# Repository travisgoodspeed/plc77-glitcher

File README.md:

Howdy y'all,

As I write this in 2021, glitching is all the rage in hardware
security again, but twenty years ago in the satellite TV cracking
community it was just as popular, with hand-etched PCBs of
through-hole components being used to glitch smart cards and freely
watch TV.

As Tripod begins to bitrot and this history slowly becomes lost to us,
I thought I'd grab an old glitcher from a [Tripod
website](http://dark-agent_drdss.tripod.com/drdss/id7.html), convert
it to Kicad, and maybe assemble a few glitchers from that age.  This
one is by LPC77, dating from April of 2001.

--Travis

## Organization

The root directory is a [Kicad](https://www.kicad.org/) project,
restored from the original design but without modernizations such as
surface-mount componenets that would alter its asthetics.

The `past` directory contains the published source files, originally
in Eagle's old binary format.  I used Eagle 6.6.0 under Wine to
convert the files into the modern XML format, which Kicad can freely
import.

## Original README Follows

Revisons:
I have increased the length of the circuit board by 1/2 inch 
to allow for a less cluttered layout.

I moved the surface mount resistors nearer to the thru hole types.

I also (the Most Significant change) modified the oscilator circuit
to add a resistor(R6) and change the value of R1, making the output
wave form much better.

Parts list and Notes

```
1 ISO card socket of your choosing
1 9 pin female D sum min connector (X2)
2 1n4004 diodes (D2, D3)
2 1n914 or 1n4148 diodes (D4, D5)
1 red/dreen led (two lead type) (D1)
1 90S2313p-10 atmel processor (IC1)programmed with bl.hex
1 MAX232 (IC3)
1 74HC00 (IC4) 
1 7405 (IC2)
1 7805T (U1)
1 bridge rectifyer (B1)
2 .1uf cap (C1, C3)
2 27pf cap (C4, C5)
1 35uf to 100 uf Cap 16v min (C2)
4 10 uf 16v cap (C6, C8, C9, C10)
2 430 to 475 ohm resister(R3 or R3a,R4 or R4a)
1 1 Meg ohm resister (R1 or R1a)
1 33ohm 1/2 watt resister (R2)
1 1K to 2.2K resister (R5 or R5a)
1 2.2K resister (R6 or R6a)
1 3.57595 mhz Crystal (Q1)
```

This programmer is intended to be used as a standalone Phoenix type
ISO programmer with the ability to use the Atmel Chip from the
Simpleboot product to allow operation with H cards that have suffered
the Black Sunday ECM.

If non Glitching operation is desired, simply do not install the Atmel
IC and put a jumper wire from pin 12 to 13 of that atmels socket.

It is designed to be built on a single sided pcb but there are a few
jumpers that must be installed.

The original one used surface mounted resister and i have added
provisions for thru hole parts, use one or the other not both!

I recommend that all the ICs be socketed.

If you wish to power the programmer from the PC, use a pc power
extension from Radio Shack and cut off one of the male plugs and
attach the red wire to the pad which goes to the diode and the black
wires to the two center pads, the yellow wire it not used but may be
soldered to the pad provided.

If powered from PC, the bridge, regulator and associated parts may be
removed.

I designed the layout to fit the four inch wide opening typical of the
diskette drive in a PC.  I mounted a programer on the plastic type
adapter used to mount a diskette drive in a 5 1/4 inch bay of a PC
with great success.

In an AT type PC it is possible to attach the comm port from the
motherboard to the internally mounted by moving the connector from the
pc's back panel or slot cover. This make for a very neat Emulation
setup.

I have added a slightly modified layout to the package that may be a
little easier to build as it is a little larger and not so
crowded. Take a look at Glitchprog1LedB.brd, the schematic is
identical so i did not duplicate it.

This is my first attempt at releasing a design so pardon my
errors. Your comments are appreiciated, I will learn from them.

 PLC77

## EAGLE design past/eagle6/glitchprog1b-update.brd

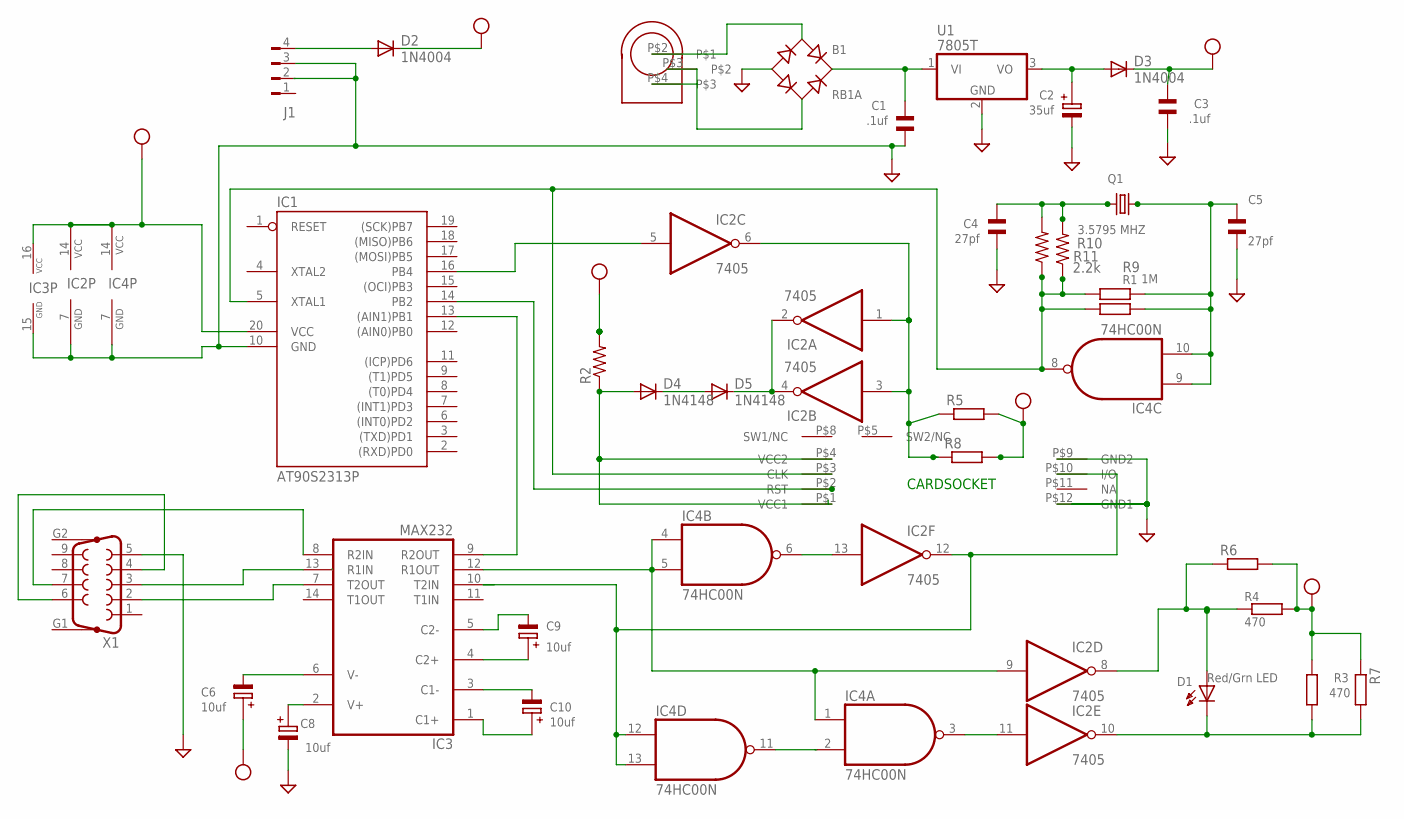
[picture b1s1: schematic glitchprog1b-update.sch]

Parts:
B1: RB1A
C1, C3: .1uf; C5B3
C2: 35uf; E2,0-5
C4, C5: 27pf; C5B3
C6, C8, C9, C10: 10uf; E2,0-5
CDR1: CHEAPREADR; CHEAPREA
D1: Red/Grn LED; LED2
D2, D3: 1N4004; DO41-10
D4, D5: 1N4148; DO35-10
IC1: AT90S2313P; DIL20
IC2: 7405; DIL14
IC3: MAX232; DIL16
IC4: 74HC00N; DIL14
J1: FLOPPY-4
Q1: 3.5795 MHZ; HC49U-V
R1: 1M; 1210
R2: R-US_0207/10; 0207/10
R3: 470; 1210
R4: 470; 1210@2
R5: R-EU_R2010; R2010
R6, R7, R8, R9: R-EU_0204/7; 0204/7
R10: R-US_0204/7; 0204/7
R11: 2.2k; M1206
U1: 7805T; TO220H
U$7: POWER1
X1: F09HP

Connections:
GND: B1.-, C1.1, C2.-, C3.1, C4.1, C5.1, C8.-, CDR1.P$9 (GND2), CDR1.P$12 (GND1), IC1.10 (GND), IC2.7 (GND), IC3.15 (GND), IC4.7 (GND), J1.3, U1.2 (GND), X1.5
unnamed: C9.-, IC3.5 (C2-)
unnamed: IC2.1 (I), IC2.3 (I), IC2.6 (O), R5.1, R8.1
unnamed: C10.-, IC3.3 (C1-)
unnamed: C10.+, IC3.1 (C1+)
unnamed: C9.+, IC3.4 (C2+)
unnamed: C6.-, IC3.6 (V-)
unnamed: C8.+, IC3.2 (V+)
unnamed: C4.2, Q1.1, R10.2, R11.2
unnamed: IC1.13 ((AIN1)PB1), IC3.9 (R2OUT)
unnamed: CDR1.P$3 (CLK), IC1.5 (XTAL1), IC4.8 (O), R1.1, R9.1, R10.1, R11.1
unnamed: D4.K (C), D5.A
unnamed: CDR1.P$2 (RST), IC1.14 (PB2)
unnamed: IC3.8 (R2IN), X1.7
unnamed: B1.+, C1.2, U1.1 (VI)
unnamed: X1.4, X1.6
unnamed: D1.A, IC2.8 (O), R4.1, R6.1
unnamed: CDR1.P$10 (I/O), IC2.12 (O), IC3.10 (T2IN), IC4.12 (I0), IC4.13 (I1)
unnamed: CDR1.P$1 (VCC1), CDR1.P$4 (VCC2), D4.A, R2.1
unnamed: IC3.7 (T2OUT), X1.2
unnamed: D5.K (C), IC2.2 (O), IC2.4 (O)
unnamed: IC2.9 (I), IC3.12 (R1OUT), IC4.1 (I0), IC4.4 (I0), IC4.5 (I1)
unnamed: D1.K, IC2.10 (O), R3.1, R7.2
unnamed: B1.AC1, U$7.P$2
unnamed: B1.AC2, U$7.P$3, U$7.P$4
unnamed: IC2.13 (I), IC4.6 (O)
unnamed: C5.2, IC4.9 (I0), IC4.10 (I1), Q1.2, R1.2, R9.2
unnamed: IC4.2 (I1), IC4.11 (O)
unnamed: IC3.13 (R1IN), X1.3
unnamed: IC1.16 (PB4), IC2.5 (I)
unnamed: IC2.11 (I), IC4.3 (O)
unnamed: C2.+, D3.A, U1.3 (VO)
unnamed: D2.A, J1.4
VCC: C3.2, C6.+, D2.K (C), D3.K (C), IC1.20 (VCC), IC2.14 (VCC), IC3.16 (VCC), IC4.14 (VCC), R2.2, R3.2, R4.2, R5.2, R6.2, R7.1, R8.2

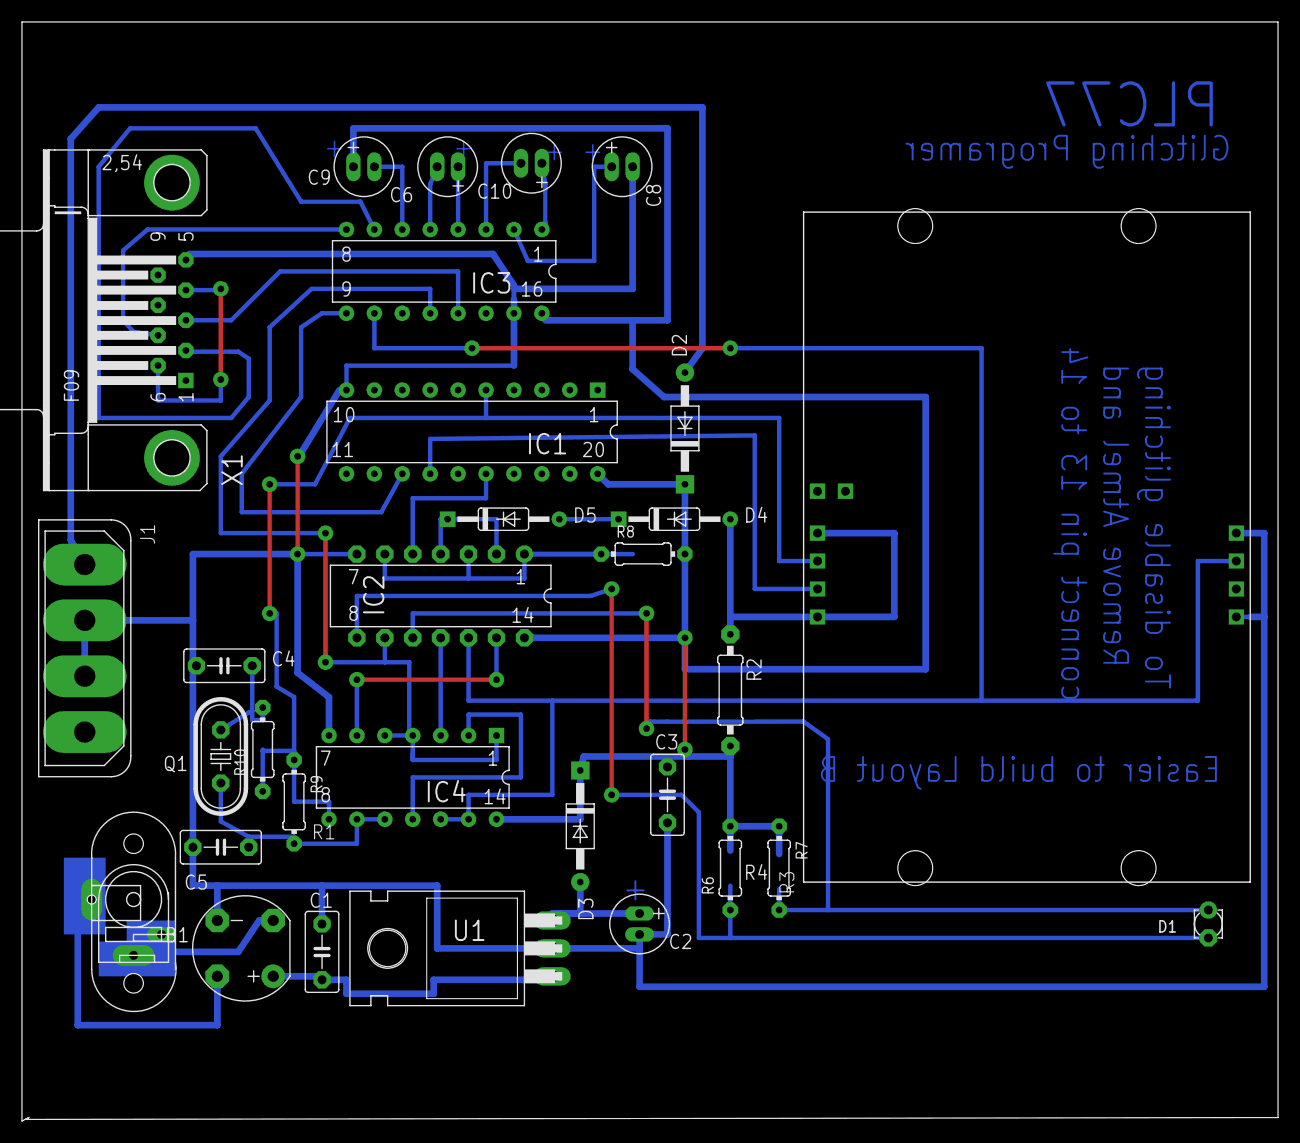
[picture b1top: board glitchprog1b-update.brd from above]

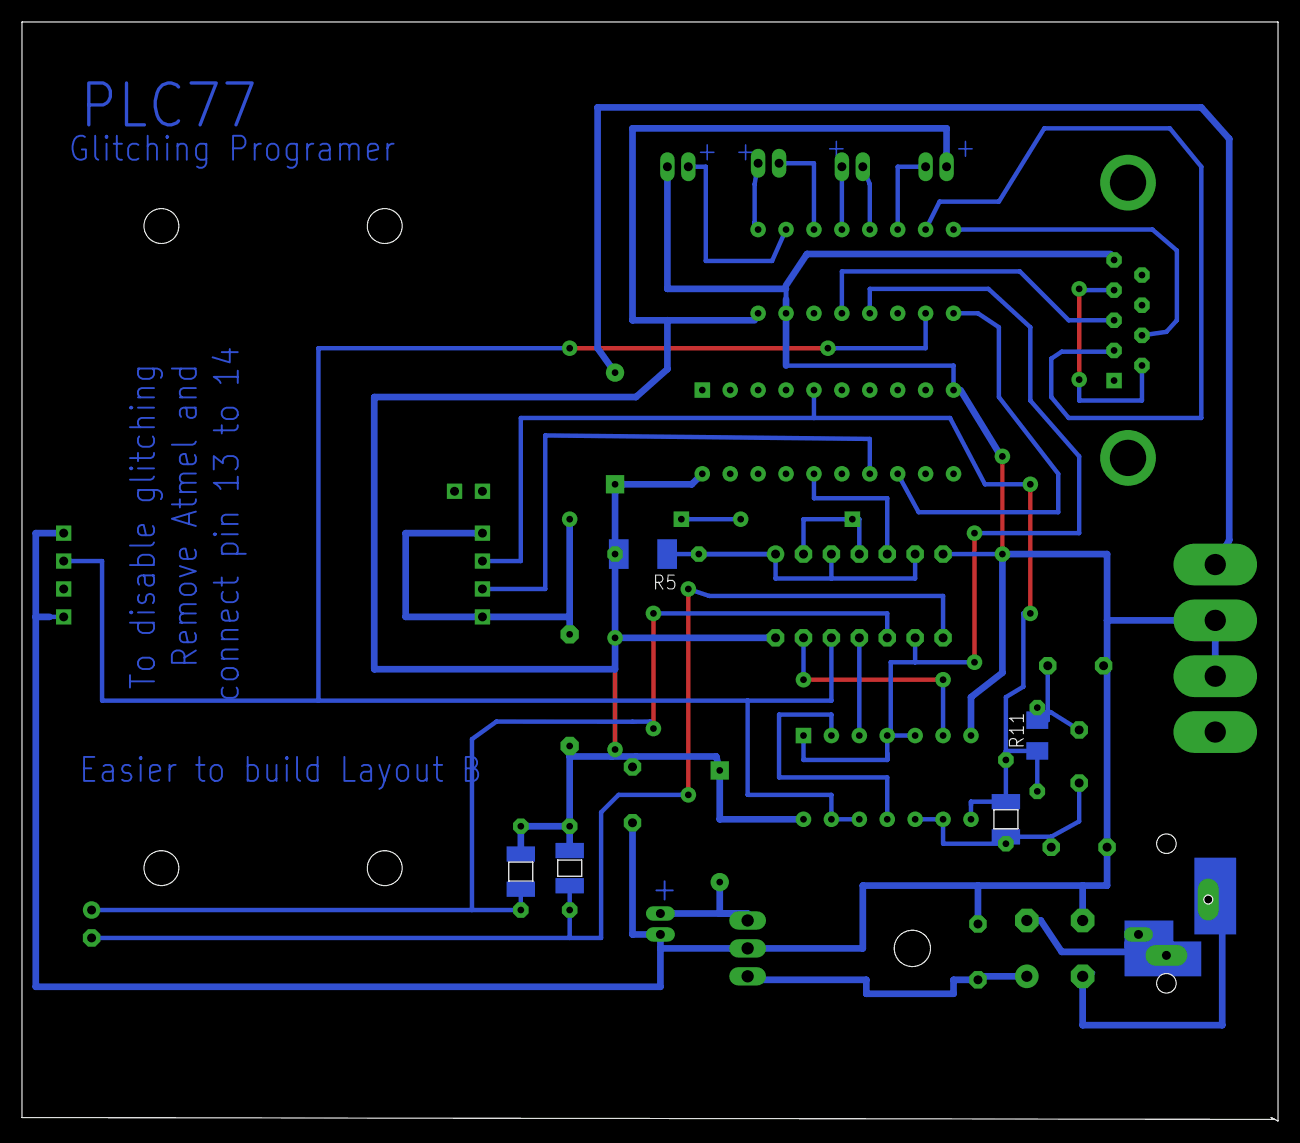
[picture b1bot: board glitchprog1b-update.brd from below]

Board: 2 copper layers, 114.3 x 100.0 mm, 36 parts (5 on the bottom side), 34 nets.

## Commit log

2021-09-09 First post.
2021-09-09 Original schematc in old Eagle format.
2021-09-09 Basic README.
2021-09-09 Eagle 6.6.0 conversion of the original files.
2021-09-09 Initial import to Kicad. Don't know if backannotation matches yet.
2021-09-09 Some 3D models and silkscreening.
2021-09-09 Rest of the README.
2021-09-09 More 3D models, minor silkscreen changes.
2021-09-09 More 3D packages.
2021-09-10 3D model for the smart card holder.
2021-09-11 Label placement.
2021-12-14 Photo of the glitcher.
2021-12-14 Update README to include photo.
2024-04-21 Snapping to grid.
